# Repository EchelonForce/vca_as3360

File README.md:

# Eurorack VCA AS3360

This is a design for a eurorack VCA using the AS3360 Dual VCA chip.

Full writeup here: https://www.robotdialogs.com/2022/09/eurorack-vca-module-as3360.html

This work is licensed under a Creative Commons Attribution-NonCommercial-ShareAlike 4.0 International License. https://creativecommons.org/licenses/by-nc-sa/4.0/

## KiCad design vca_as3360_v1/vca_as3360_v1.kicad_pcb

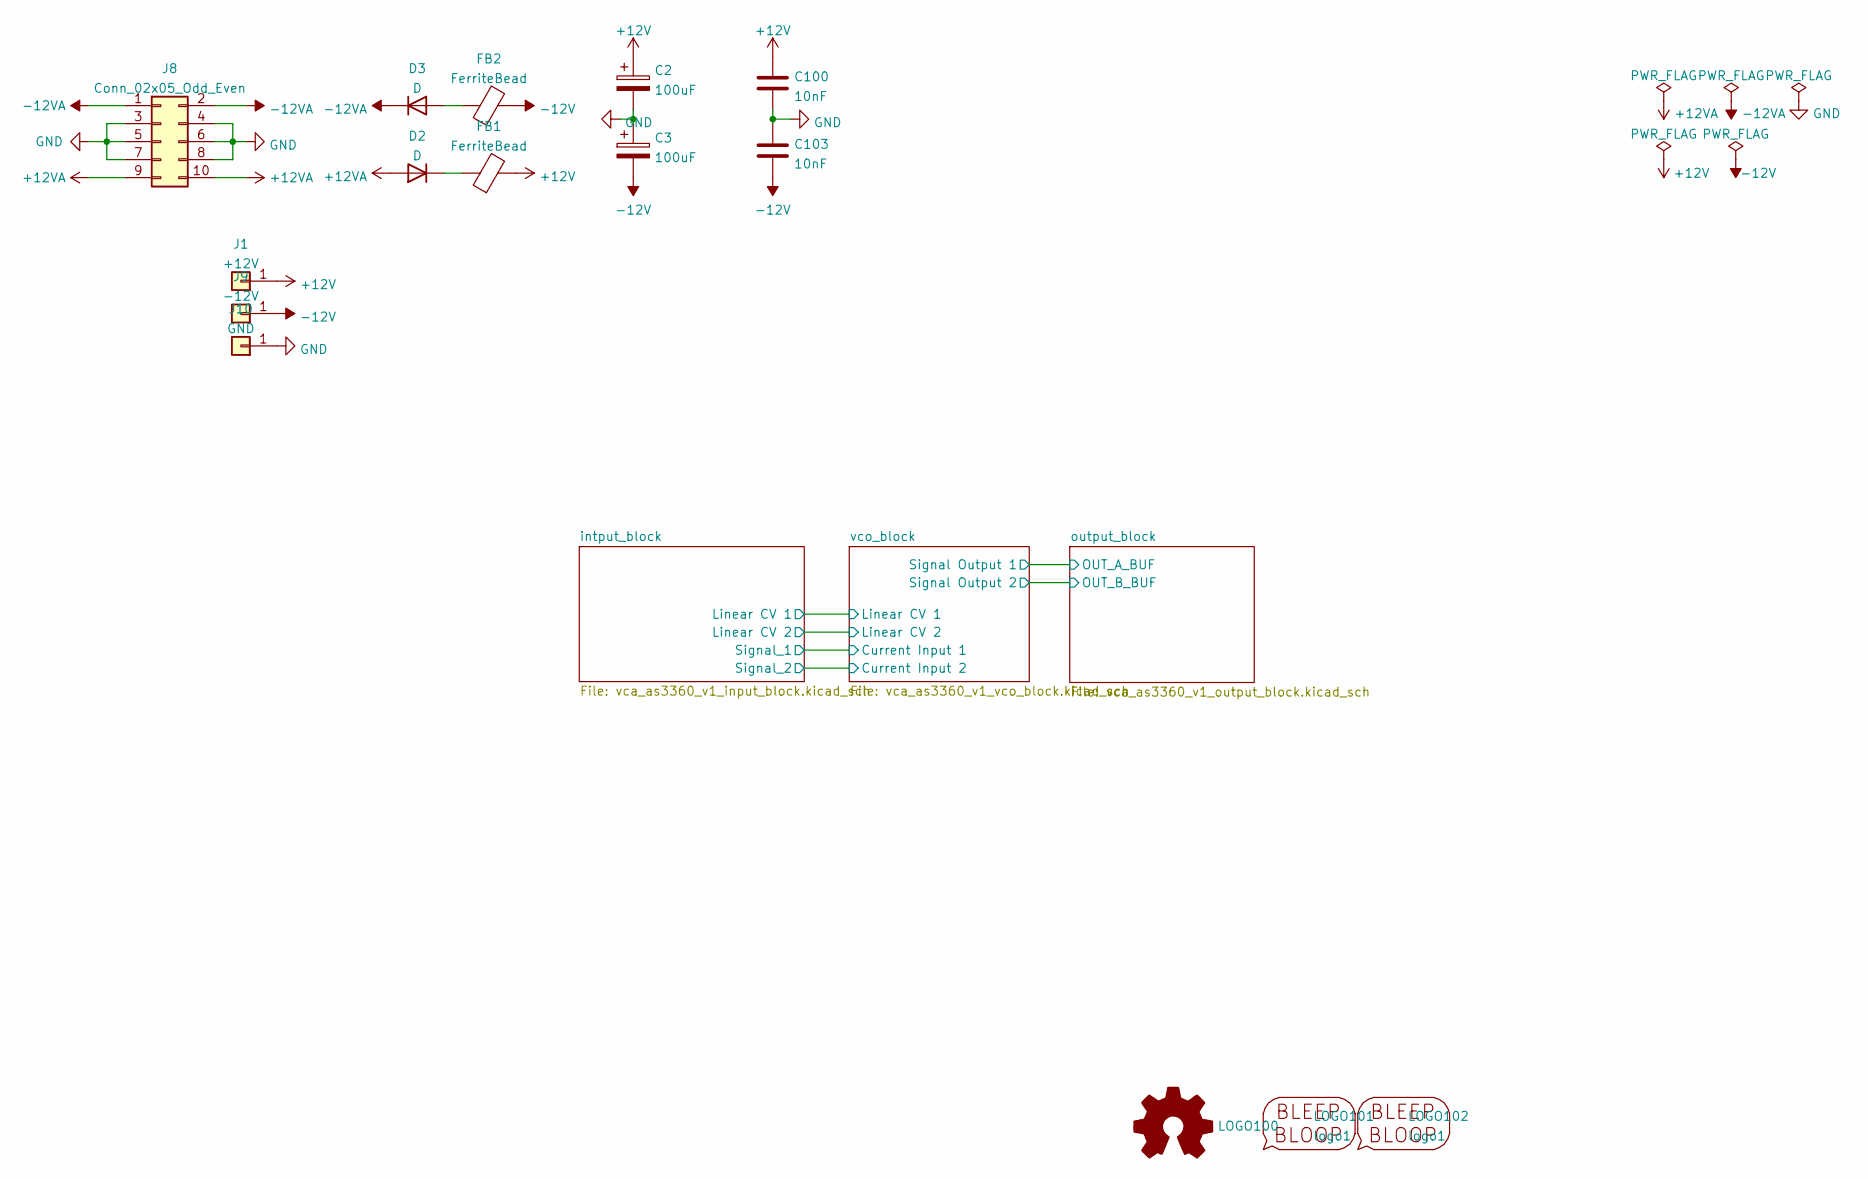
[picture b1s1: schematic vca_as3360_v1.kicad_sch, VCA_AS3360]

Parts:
C2, C3: 100uF; CP_Radial_D5.0mm_P2.50mm
C100, C103: 10nF; C_1206_3216Metric_Pad1.33x1.80mm_HandSolder
D2, D3: D; D_A-405_P2.54mm_Vertical_KathodeUp
FB1, FB2: FerriteBead; L_Axial_L6.6mm_D2.7mm_P2.54mm_Vertical_Vishay_IM-2
J1: +12V; PinHeader_1x01_P2.54mm_Vertical
J8: Conn_02x05_Odd_Even; IDC-Header_2x05_P2.54mm_Vertical
J9: -12V; PinHeader_1x01_P2.54mm_Vertical
J10: GND; PinHeader_1x01_P2.54mm_Vertical
LOGO100: Logo_Open_Hardware_Small; OSHW-Symbol_6.7x6mm_SilkScreen
LOGO101: logo1; Logo1
LOGO102: logo1; Logo2

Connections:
+12V: C2.1, C100.1, FB1.2, J1.1; also elsewhere on the board
+12VA: D2.2 (A), J8.9, J8.10
-12V: C3.2, C103.2, FB2.2, J9.1; also elsewhere on the board
-12VA: D3.1 (K), J8.1, J8.2
GND: C2.2, C3.1, C100.2, C103.1, J8.3, J8.4, J8.5, J8.6, J8.7, J8.8, J10.1; also elsewhere on the board
unnamed: D2.1 (K), FB1.1
unnamed: D3.2 (A), FB2.1

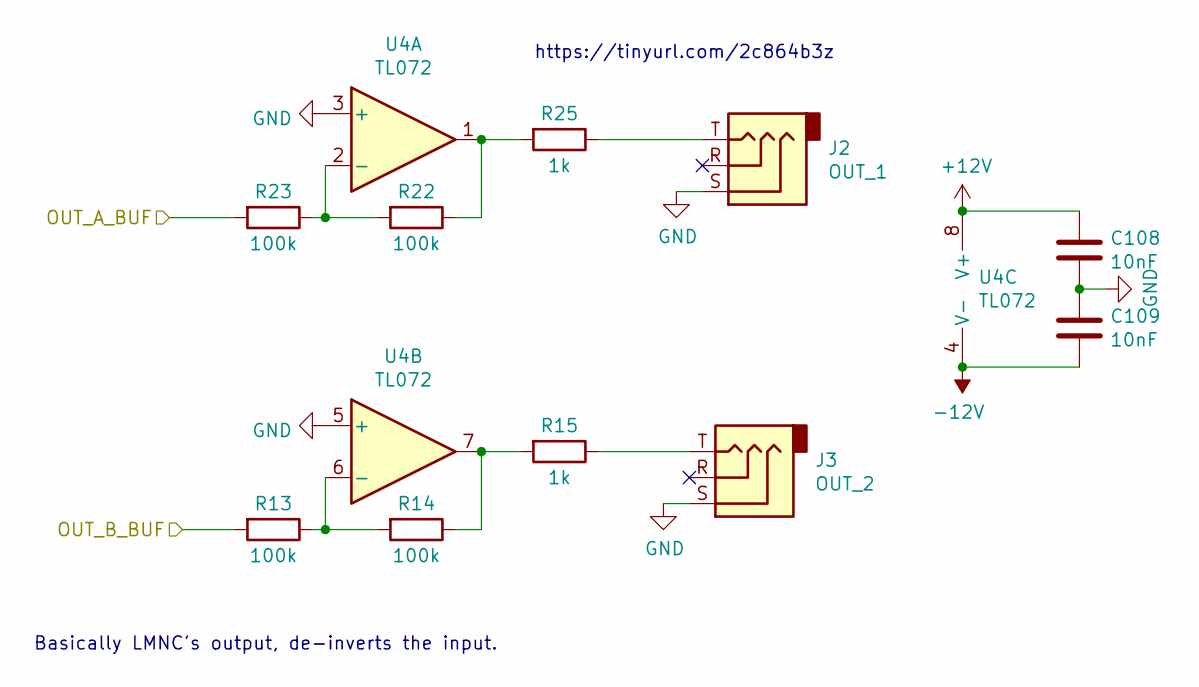
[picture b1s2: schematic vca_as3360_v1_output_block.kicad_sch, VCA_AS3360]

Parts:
C108, C109: 10nF; C_1206_3216Metric_Pad1.33x1.80mm_HandSolder
J2: OUT_1; Jack_3.5mm_MJ-355W_Vertical
J3: OUT_2; Jack_3.5mm_MJ-355W_Vertical
R13, R14, R22, R23: 100k; R_1206_3216Metric_Pad1.30x1.75mm_HandSolder
R15, R25: 1k; R_1206_3216Metric_Pad1.30x1.75mm_HandSolder
U4: TL072; DIP-8_W7.62mm_Socket_LongPads

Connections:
+12V: C108.2, U4.8 (V+); also elsewhere on the board
-12V: C109.1, U4.4 (V-); also elsewhere on the board
/output_block/OUT_A_BUF: R23.2; also elsewhere on the board
/output_block/OUT_B_BUF: R13.2; also elsewhere on the board
GND: C108.1, C109.2, J2.S, J3.S, U4.3 (+), U4.5 (+); also elsewhere on the board
unnamed: J2.T, R25.1
unnamed: J3.T, R15.1
unnamed: R14.1, R15.2, U4.7
unnamed: R13.1, R14.2, U4.6 (-)
unnamed: R22.2, R23.1, U4.2 (-)
unnamed: R22.1, R25.2, U4.1

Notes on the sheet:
Basically LMNC's output, de-inverts the input.
https://tinyurl.com/2c864b3z

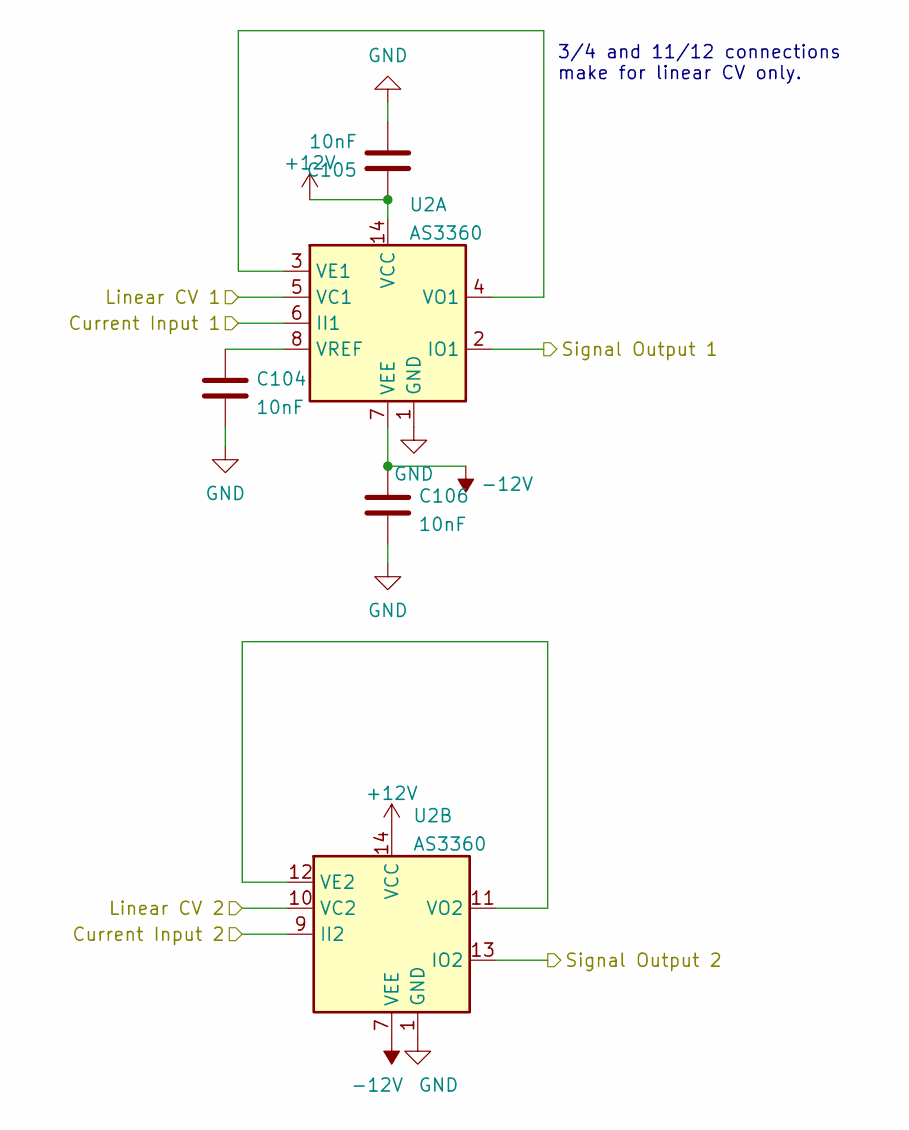
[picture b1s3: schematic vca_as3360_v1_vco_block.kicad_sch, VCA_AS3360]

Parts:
C104, C105, C106: 10nF; C_1206_3216Metric_Pad1.33x1.80mm_HandSolder
U2: AS3360; DIP-14_W7.62mm_Socket_LongPads

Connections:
+12V: C105.1, U2.14 (VCC); also elsewhere on the board
-12V: C106.1, U2.7 (VEE); also elsewhere on the board
/intput_block/Linear CV 1: U2.5 (VC1); also elsewhere on the board
/intput_block/Linear CV 2: U2.10 (VC2); also elsewhere on the board
/intput_block/Signal_1: U2.6 (II1); also elsewhere on the board
/intput_block/Signal_2: U2.9 (II2); also elsewhere on the board
/output_block/OUT_A_BUF: U2.2 (IO1); also elsewhere on the board
/output_block/OUT_B_BUF: U2.13 (IO2); also elsewhere on the board
GND: C104.2, C105.2, C106.2, U2.1 (GND); also elsewhere on the board
unnamed: C104.1, U2.8 (VREF)
unnamed: U2.3 (VE1), U2.4 (VO1)
unnamed: U2.11 (VO2), U2.12 (VE2)

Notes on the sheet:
3/4 and 11/12 connections make for linear CV only.

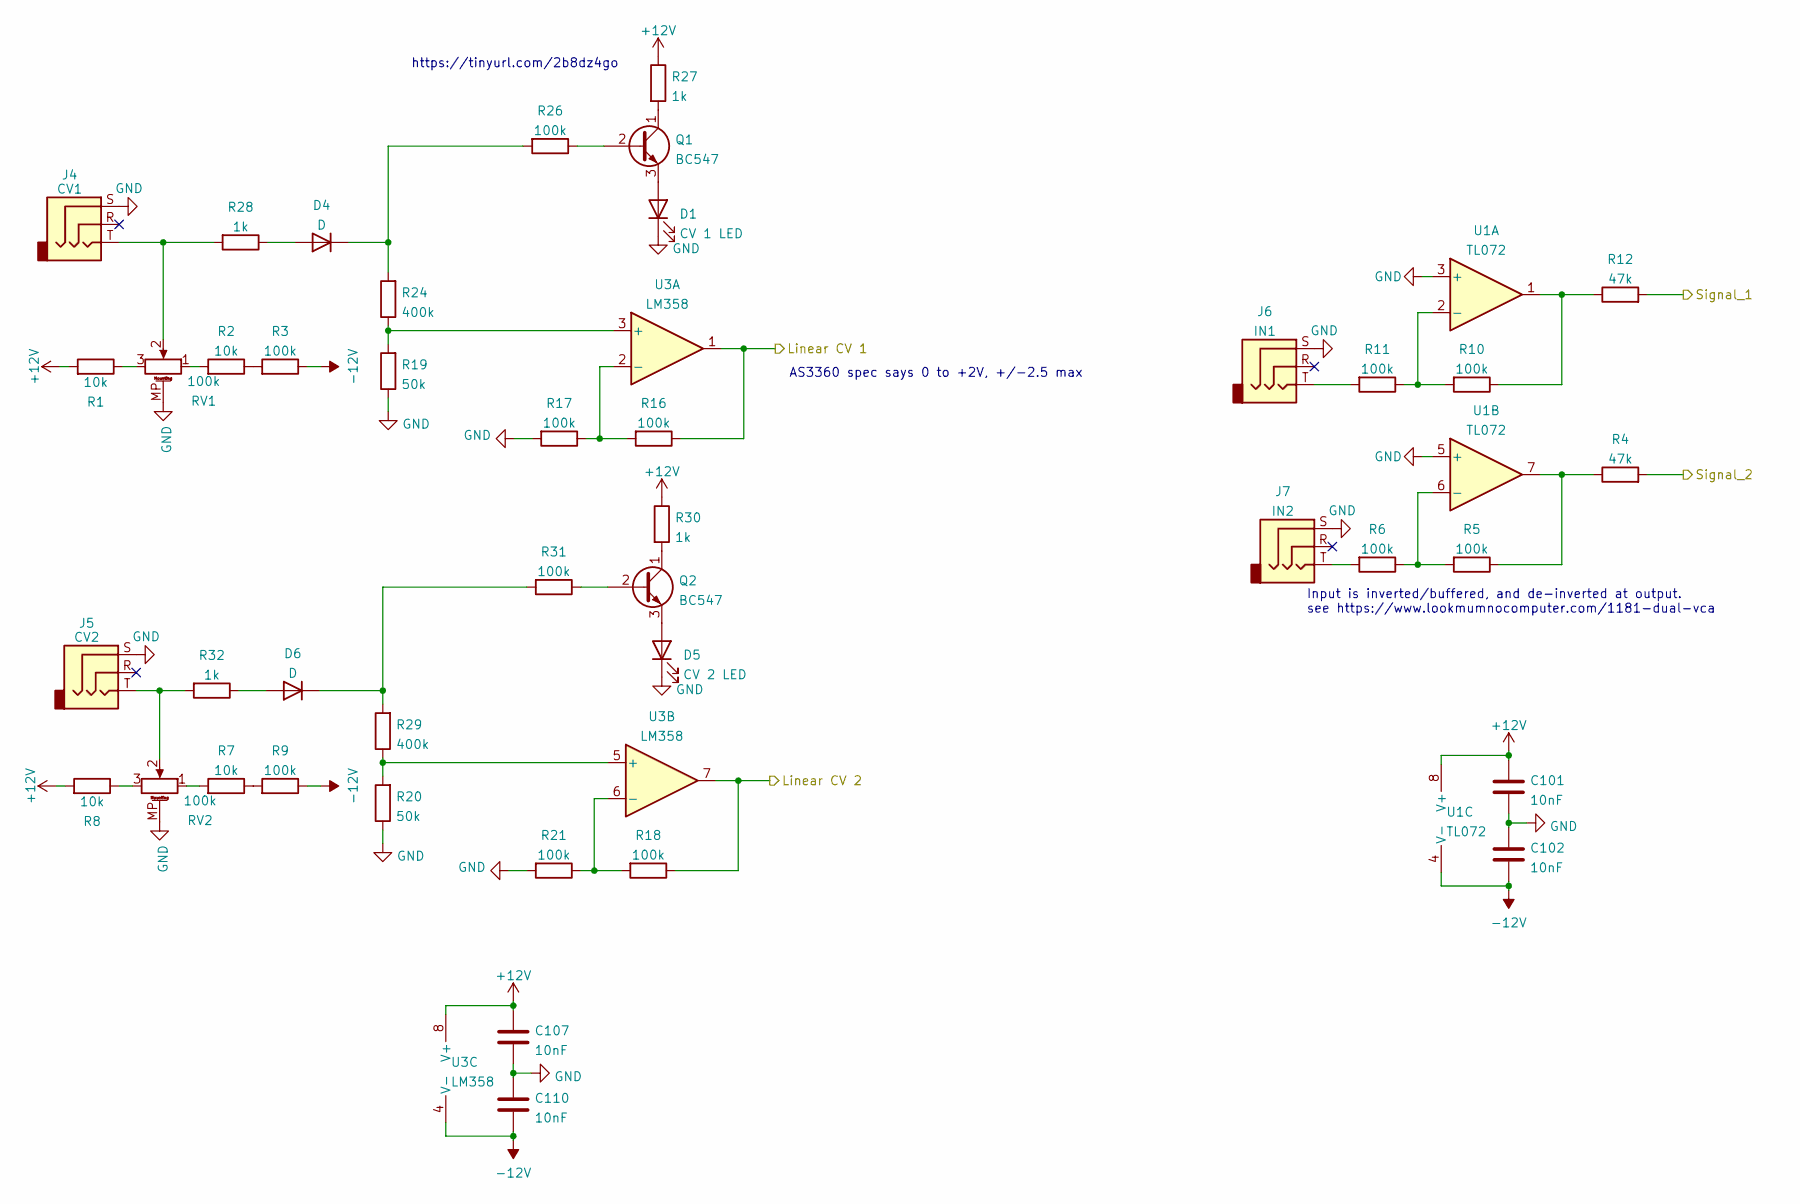
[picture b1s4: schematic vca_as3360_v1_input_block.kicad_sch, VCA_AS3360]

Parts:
C101, C102, C107, C110: 10nF; C_1206_3216Metric_Pad1.33x1.80mm_HandSolder
D1: CV 1 LED; LED_D3.0mm
D4, D6: D; D_A-405_P2.54mm_Vertical_KathodeUp
D5: CV 2 LED; LED_D3.0mm
J4: CV1; Jack_3.5mm_MJ-355W_Vertical
J5: CV2; Jack_3.5mm_MJ-355W_Vertical
J6: IN1; Jack_3.5mm_MJ-355W_Vertical
J7: IN2; Jack_3.5mm_MJ-355W_Vertical
Q1, Q2: BC547; TO-92_Inline_Wide
R1, R2, R7, R8: 10k; R_1206_3216Metric_Pad1.30x1.75mm_HandSolder
R3, R5, R6, R9, R10, R11, R16, R17, R18, R21, R26, R31: 100k; R_1206_3216Metric_Pad1.30x1.75mm_HandSolder
R4, R12: 47k; R_1206_3216Metric_Pad1.30x1.75mm_HandSolder
R19, R20: 50k; R_1206_3216Metric_Pad1.30x1.75mm_HandSolder
R24, R29: 400k; R_1206_3216Metric_Pad1.30x1.75mm_HandSolder
R27, R28, R30, R32: 1k; R_1206_3216Metric_Pad1.30x1.75mm_HandSolder
RV1, RV2: 100k; Potentiometer_Alpha_RD901F-40-00D_Single_Vertical_w_3d
U1: TL072; DIP-8_W7.62mm_Socket_LongPads
U3: LM358; DIP-8_W7.62mm_Socket_LongPads

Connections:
+12V: C101.1, C107.1, R1.2, R8.2, R27.1, R30.1, U1.8 (V+), U3.8 (V+); also elsewhere on the board
-12V: C102.2, C110.2, R3.1, R9.1, U1.4 (V-), U3.4 (V-); also elsewhere on the board
/intput_block/Linear CV 1: R16.1, U3.1; also elsewhere on the board
/intput_block/Linear CV 2: R18.1, U3.7; also elsewhere on the board
/intput_block/Signal_1: R12.2; also elsewhere on the board
/intput_block/Signal_2: R4.2; also elsewhere on the board
GND: C101.2, C102.1, C107.2, C110.1, D1.1 (K), D5.1 (K), J4.S, J5.S, J6.S, J7.S, R17.2, R19.1, R20.1, R21.2, RV1.MP (MountPin), RV2.MP (MountPin), U1.3 (+), U1.5 (+); also elsewhere on the board
unnamed: D1.2 (A), Q1.3 (E)
unnamed: D4.1 (K), R24.2, R26.2
unnamed: D4.2 (A), R28.1
unnamed: D5.2 (A), Q2.3 (E)
unnamed: D6.1 (K), R29.2, R31.2
unnamed: D6.2 (A), R32.1
unnamed: J4.T, R28.2, RV1.2
unnamed: J5.T, R32.2, RV2.2
unnamed: J6.T, R11.2
unnamed: J7.T, R6.2
unnamed: Q1.1 (C), R27.2
unnamed: Q1.2 (B), R26.1
unnamed: Q2.1 (C), R30.2
unnamed: Q2.2 (B), R31.1
unnamed: R1.1, RV1.3
unnamed: R2.2, RV1.1
unnamed: R2.1, R3.2
unnamed: R4.1, R5.1, U1.7
unnamed: R5.2, R6.1, U1.6 (-)
unnamed: R7.1, R9.2
unnamed: R7.2, RV2.1
unnamed: R8.1, RV2.3
unnamed: R10.2, R11.1, U1.2 (-)
unnamed: R10.1, R12.1, U1.1
unnamed: R16.2, R17.1, U3.2 (-)
unnamed: R18.2, R21.1, U3.6 (-)
unnamed: R19.2, R24.1, U3.3 (+)
unnamed: R20.2, R29.1, U3.5 (+)

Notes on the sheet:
Input is inverted/buffered, and de-inverted at output. see https://www.lookmumnocomputer.com/1181-dual-vca
AS3360 spec says 0 to +2V, +/-2.5 max
https://tinyurl.com/2b8dz4go

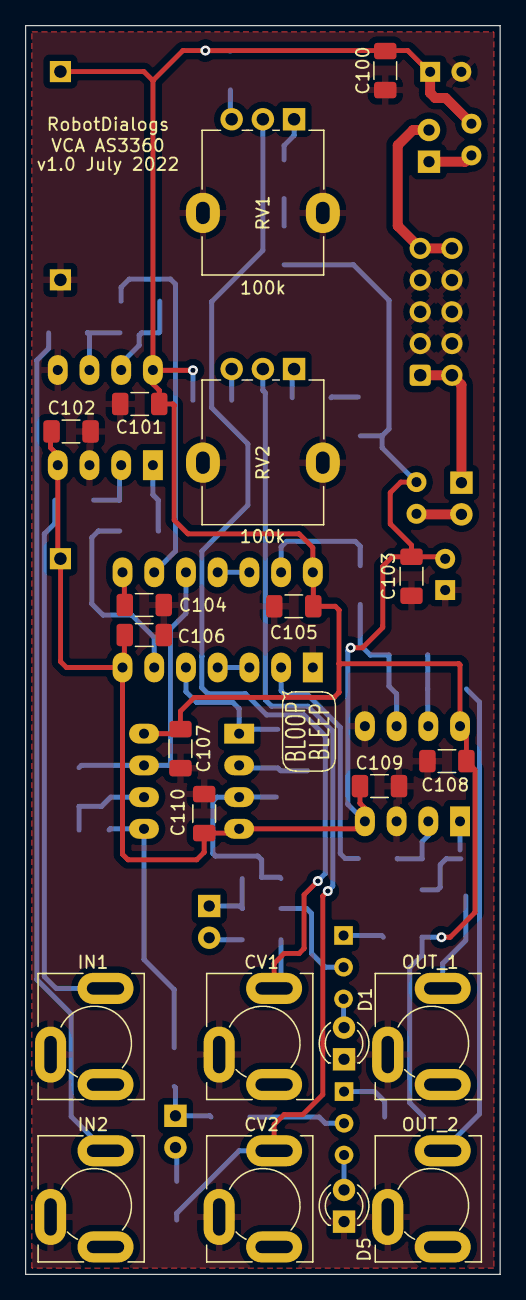
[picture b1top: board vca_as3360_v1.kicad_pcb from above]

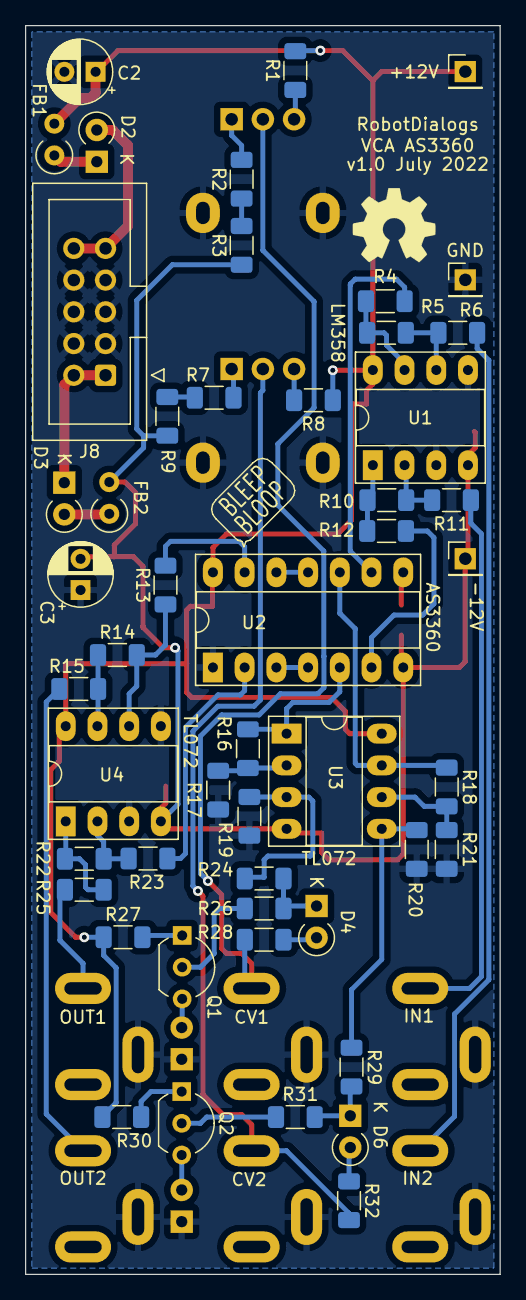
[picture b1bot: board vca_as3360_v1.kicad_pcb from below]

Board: 2 copper layers, 38.0 x 100.0 mm, 74 parts (51 on the bottom side), 50 nets.

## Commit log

2022-07-16 Initial commit with .gitignore
2022-07-16 Schematic mostly figured out, not yet breadboarded
2022-07-31 Layout and routing first pass done
2022-07-31 Geographic rename and silkscreen cleanup
2022-07-31 Add jumper points for passing power to another pcb
2022-08-10 Fix pcb title block
2022-09-09 Add front panel files
2022-09-09 Add readme, notes and schematic pdf
2022-09-09 panelized outputs for v1
